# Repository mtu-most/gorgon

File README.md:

<H1>Gorgon is a big printer with multiple heads</H1>
All things Gorgon printer

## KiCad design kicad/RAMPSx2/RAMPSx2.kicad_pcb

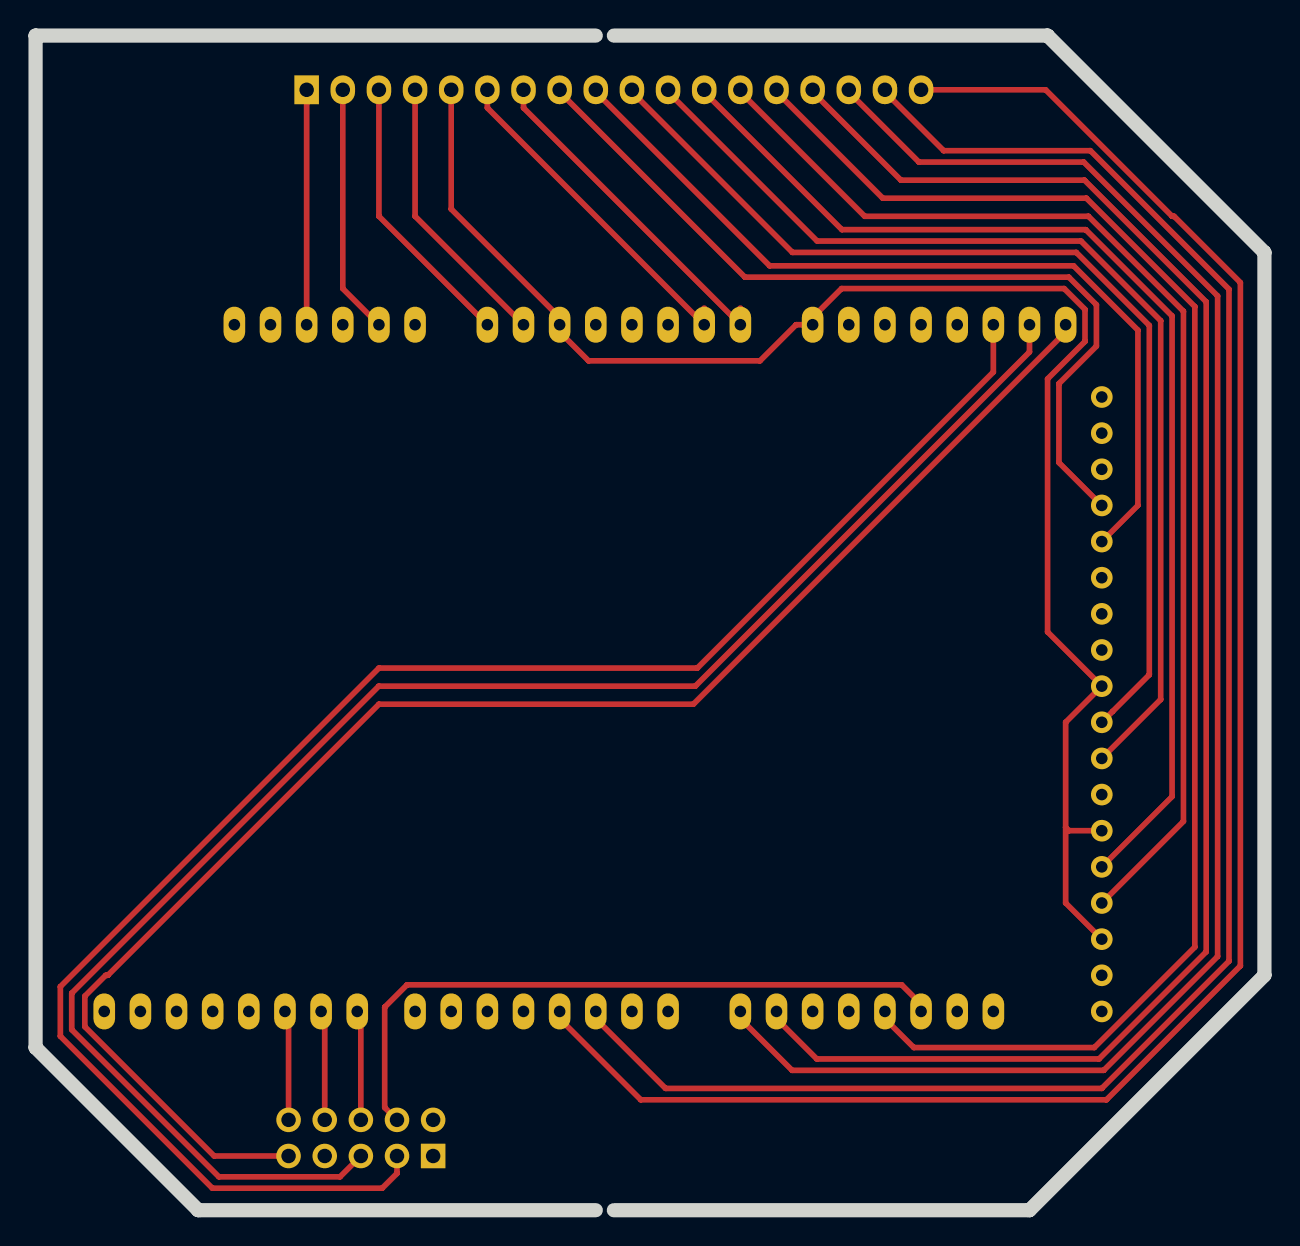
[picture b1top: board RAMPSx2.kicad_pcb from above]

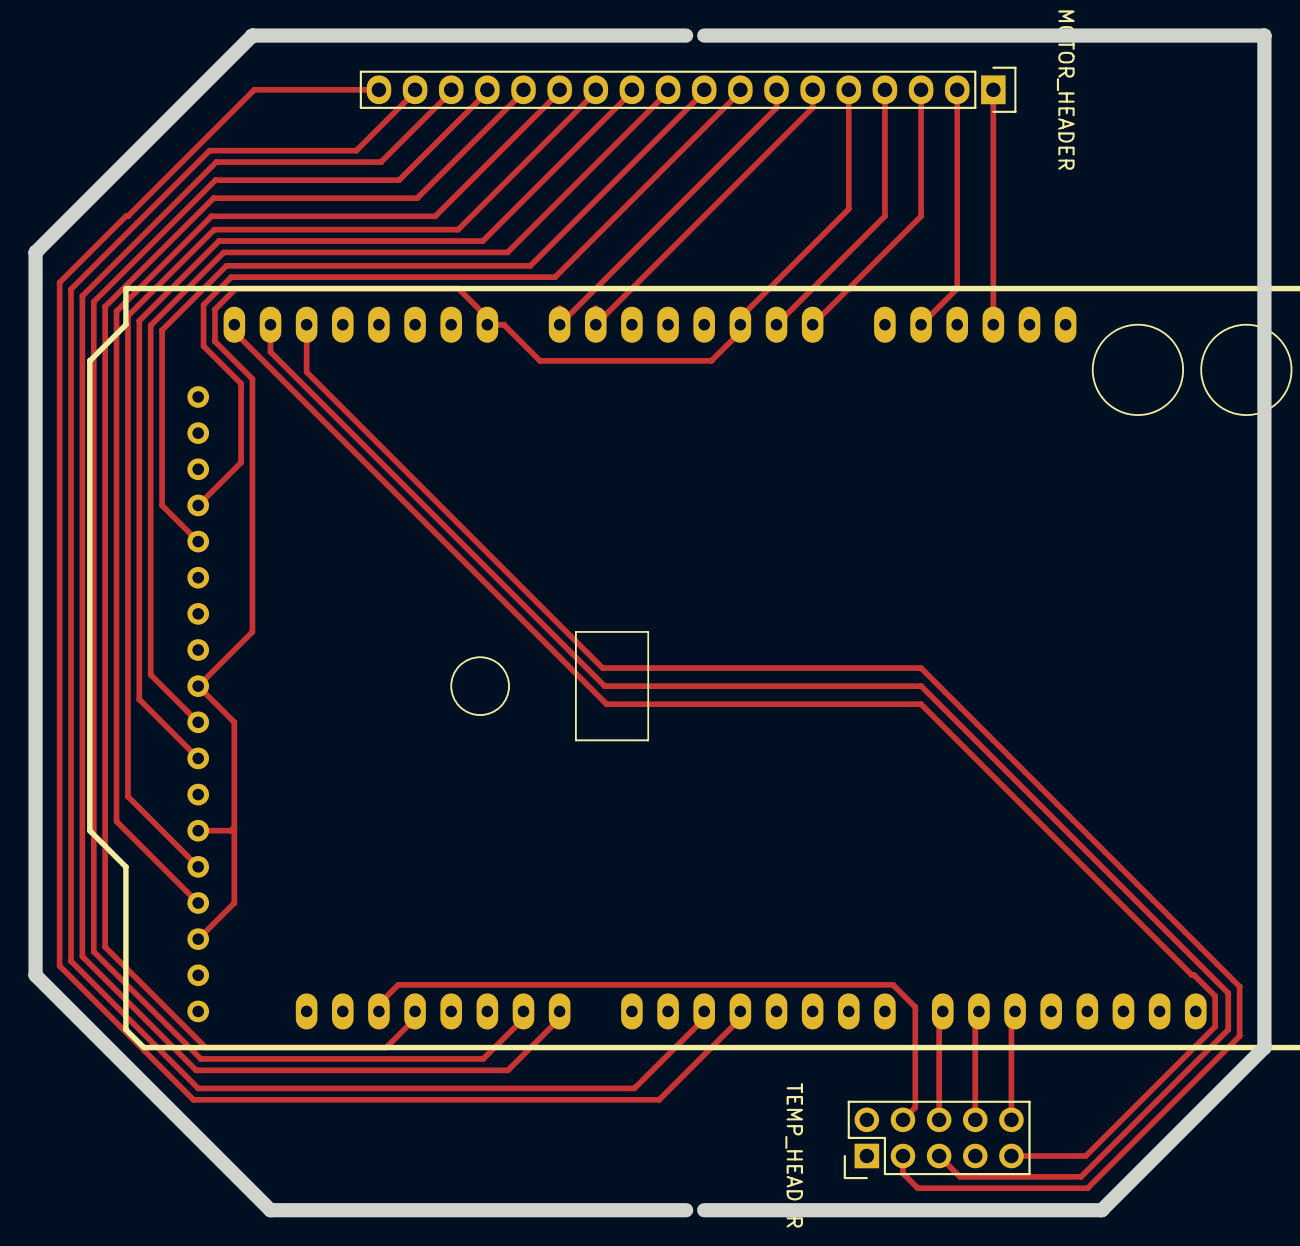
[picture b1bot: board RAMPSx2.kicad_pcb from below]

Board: 2 copper layers, 86.4 x 82.5 mm, 3 parts (3 on the bottom side), 25 nets.

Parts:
MOTOR_HEADER: Pin_Headers:Pin_Header_Straight_1x18; Pin_Header_Straight_1x18
RAMPS: arduino_shields:ARDUINO_MEGA_SHIELD; ARDUINO_MEGA_SHIELD
TEMP_HEADER: Pin_Headers:Pin_Header_Straight_2x05; Pin_Header_Straight_2x05

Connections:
2: MOTOR_HEADER.17, RAMPS.2
3: MOTOR_HEADER.18, RAMPS.3
5V: MOTOR_HEADER.1, RAMPS.5V
8: RAMPS.8, TEMP_HEADER.6
9: RAMPS.9, TEMP_HEADER.8
10: RAMPS.10, TEMP_HEADER.10
14: MOTOR_HEADER.16, RAMPS.14
15: MOTOR_HEADER.15, RAMPS.15
18: MOTOR_HEADER.14, RAMPS.18
19: RAMPS.19, TEMP_HEADER.4
26: MOTOR_HEADER.13, RAMPS.26
28: MOTOR_HEADER.12, RAMPS.28
34: MOTOR_HEADER.11, RAMPS.34
36: MOTOR_HEADER.10, RAMPS.36
38: MOTOR_HEADER.5, RAMPS.24, RAMPS.30, RAMPS.38, RAMPS.AD2, RAMPS.AD8
46: MOTOR_HEADER.9, RAMPS.46
48: MOTOR_HEADER.8, RAMPS.48
AD0: MOTOR_HEADER.3, RAMPS.AD0
AD1: MOTOR_HEADER.4, RAMPS.AD1
AD6: MOTOR_HEADER.6, RAMPS.AD6
AD7: MOTOR_HEADER.7, RAMPS.AD7
AD13: RAMPS.AD13, TEMP_HEADER.3
AD14: RAMPS.AD14, TEMP_HEADER.5
AD15: RAMPS.AD15, TEMP_HEADER.9
GND: MOTOR_HEADER.2, RAMPS.GND2

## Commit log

2016-01-04 initial
2016-01-04 various updates and electronics
2016-01-26 updated scads
